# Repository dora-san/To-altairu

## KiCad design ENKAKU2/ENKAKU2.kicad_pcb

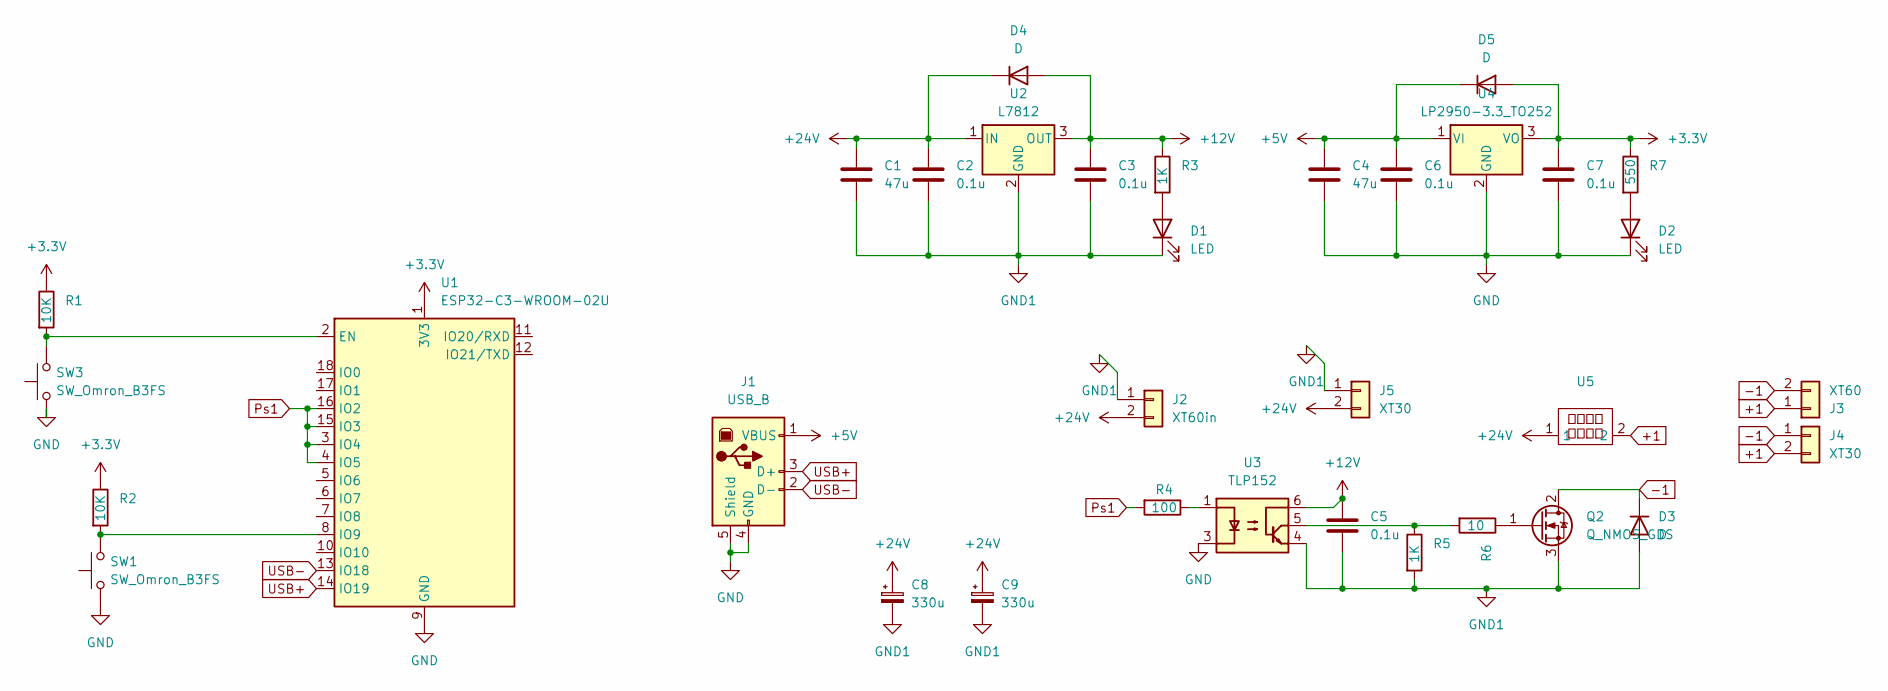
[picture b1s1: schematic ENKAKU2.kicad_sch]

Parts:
C1, C4: 47u; C_0603_1608Metric
C2, C3, C5, C6, C7: 0.1u; C_0603_1608Metric
C8, C9: 330u; CP_Elec_10x10
D1, D2: LED; LED_0603_1608Metric
D3, D4, D5: D; D_SOD-128
J1: USB_B; USB_B_Lumberg_2411_02_Horizontal
J2: XT60in; AMASS_XT60IPW-M_1x03_P7.20mm_Horizontal
J3: XT60; AMASS_XT60PW-F_1x02_P7.20mm_Horizontal
J4, J5: XT30; AMASS_XT30PW-F_1x02_P2.50mm_Horizontal
Q2: Q_NMOS_GDS; TO-263-2
R1, R2: 10K; R_0603_1608Metric
R3, R5: 1K; R_0603_1608Metric
R4: 100; R_0603_1608Metric
R6: 10; R_0603_1608Metric
R7: 550; R_0603_1608Metric
SW1, SW3: SW_Omron_B3FS; SW_PUSH-12mm
U1: ESP32-C3-WROOM-02U
U2: L7812; TO-252-2
U3: TLP152; MFSOP6-5_4.4x3.6mm_P1.27mm
U4: LP2950-3.3_TO252; TO-252-2
U5: XS-506A

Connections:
+1: J3.1, J4.2, U5.2
+3.3V: C7.1, D5.2 (A), R1.1, R2.1, R7.1, U1.1 (3V3), U4.3 (VO)
+5V: C4.1, C6.1, D5.1 (K), J1.1 (VBUS), U4.1 (VI)
+12V: C3.1, C5.1, D4.2 (A), R3.1, U2.3 (OUT), U3.6
+24V: C1.1, C2.1, C8.1, C9.1, D4.1 (K), J2.2, J5.2, U2.1 (IN), U5.1
-1: D3.1 (K), J3.2, J4.1, Q2.2 (D)
GND: C4.2, C6.2, C7.2, D2.1 (K), J1.4 (GND), J1.5 (Shield), SW1.1, SW3.1, U1.9 (GND), U1.19 (GND), U3.3, U4.2 (GND)
GND1: C1.2, C2.2, C3.2, C5.2, C8.2, C9.2, D1.1 (K), D3.2 (A), J2.1, J5.1, Q2.3 (S), R5.2, U2.2 (GND), U3.4
unnamed: D1.2 (A), R3.2
unnamed: D2.2 (A), R7.2
unnamed: Q2.1 (G), R6.1
unnamed: R4.1, U3.1
unnamed: R5.1, R6.2, U3.5
unnamed: R1.2, SW3.2, U1.2 (EN)
unnamed: R2.2, SW1.2, U1.8 (IO9)
Ps1: R4.2, U1.3 (IO4), U1.4 (IO5), U1.15 (IO3), U1.16 (IO2)
USB+: J1.3 (D+), U1.14 (IO19)
USB-: J1.2 (D-), U1.13 (IO18)

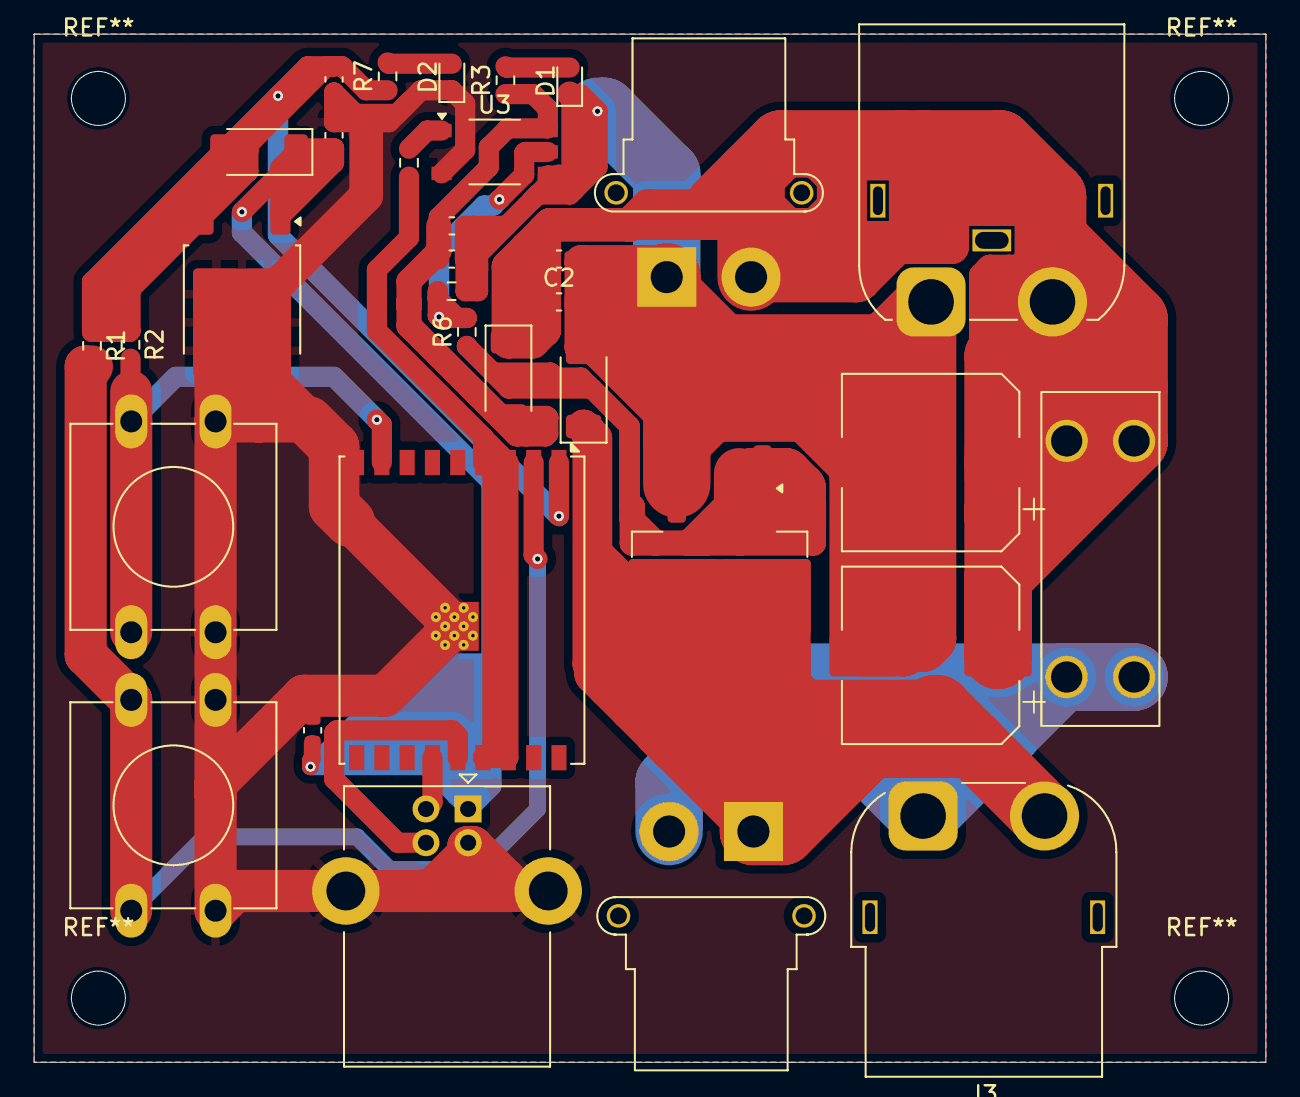
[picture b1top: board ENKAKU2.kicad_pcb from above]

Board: 2 copper layers, 73.0 x 61.0 mm, 33 parts (0 on the bottom side), 18 nets.
